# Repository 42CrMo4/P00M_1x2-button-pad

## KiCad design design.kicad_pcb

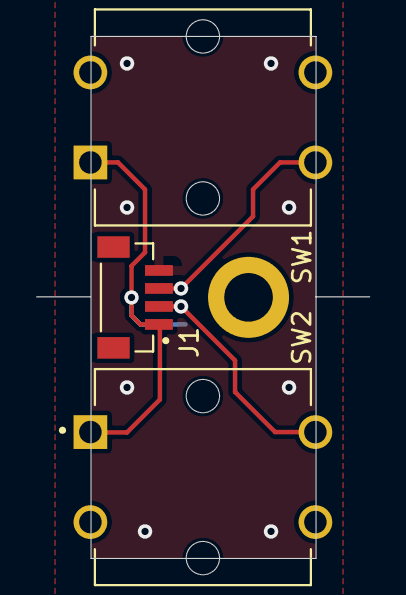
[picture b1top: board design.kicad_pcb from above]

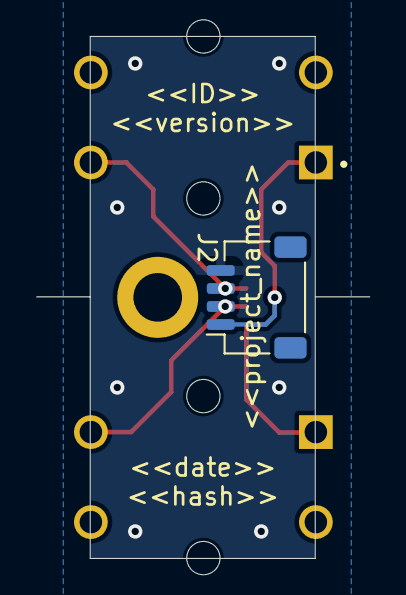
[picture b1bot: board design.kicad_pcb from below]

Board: 2 copper layers, 12.5 x 29.0 mm, 5 parts (2 on the bottom side), 4 nets.

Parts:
H1: MountingHole; MountingHole_2.7mm_M2.5_ISO7380_Pad
J1: BM04B-SRSS-TB_LF__SN_; BM04B-SRSS-TB_LF__SN__JST_BM04B-SRSS-TB_LF__SN_
J2: SM04B-SRSS-TB_LF__SN_; JST_SH_SM04B-SRSS-TB_1x04-1MP_P1.00mm_Horizontal
SW1, SW2: SW_Push; B3F-4055_SW_B3F-4055

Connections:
B1: J1.2, J2.2, SW2.2
B2: J1.3, J2.3, SW1.2
GND: J1.4, J2.4
VCC: J1.1, J2.1, SW1.1, SW2.1

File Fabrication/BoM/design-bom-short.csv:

Row,Description,Part,References,Value,Footprint,Quantity Per PCB,Status,Datasheet,MF,MAXIMUM_PACKAGE_HEIGHT,Package,Price,Check_prices,STANDARD,PARTREV,SnapEDA_Link,MP,MANUFACTURER,Availability,SNAPEDA_PN
1,Connector Header Surface Mount 4 position 0.039 (1.00mm),BM04B-SRSS-TB_LF__SN_,J1,BM04B-SRSS-TB_LF__SN_,BM04B-SRSS-TB_LF__SN__JST_BM04B-SRSS-TB_LF__SN_,1, ,,JST Sales,6.3 mm,None,None,https://www.snapeda.com/parts/BM04B-SRSS-TB(LF)(SN)/JST+Sale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,Manufacturer Recommendations,N/A,https://www.snapeda.com/parts/BM04B-SRSS-TB(LF)(SN)/JST+Sale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,BM04B-SRSS-TB(LF)(SN),JST Sales America Inc.,In Stock,BM04B-SRSS-TB(LF)(SN)
2,Connector Header Surface Mount 4 position 0.039 (1.00mm),BM04B-SRSS-TB_LF__SN_,J2,SM04B-SRSS-TB_LF__SN_,JST_SH_SM04B-SRSS-TB_1x04-1MP_P1.00mm_Horizontal,1, ,,JST Sales,6.3 mm,None,None,https://www.snapeda.com/parts/BM04B-SRSS-TB(LF)(SN)/JST+Sale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,Manufacturer Recommendations,N/A,https://www.snapeda.com/parts/BM04B-SRSS-TB(LF)(SN)/JST+Sale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,BM04B-SRSS-TB(LF)(SN),JST Sales America Inc.,In Stock,BM04B-SRSS-TB(LF)(SN)
3,,SW_Push,SW1 SW2,SW_Push,B3F-4055_SW_B3F-4055,2, ,~,,,,,,,,,,,,

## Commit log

2025-10-04 DEL template stuff
2025-10-04 init
2025-10-12 cahnge to kicad 9.x and updates
2025-10-12 add 3d models
2025-10-12 Update Bom and PCB_top
2025-10-12 Archive & Renew release docs
